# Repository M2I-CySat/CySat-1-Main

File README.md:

# CySat 1 - Make to Innovate at Iowa State University

**Onboard Computer (OBC) firmware, Satellite Systems, and Ground Station Software** - [CySat M2I](https://m2i.aere.iastate.edu/cysat/)

## Instructions
1. Navigate to the CySat-1 CyBox folder and read the documents under `/About CySat-1: README!` to gain a basic understanding of the CySat-1 mission, objectives, and project structure 
2. Continue reading this README to know basic files, instructions, and applications for each subsystem
3. Reference subsystem-specific setup instructions, guides, and data sheets to gain an understanding of your specific tasks found in the [CySat 1 box folder](https://iastate.app.box.com/folder/174137892065) under Subsystems -> [Subsystem]

## ADCS - Attitude Determination and Control System

**ADCS Testing Spreadsheets now in Box: Subsystems/ADCS/Tests**

- `CubeADCS - Commissioning Manual [V3.06]` - This document describes the activities related to the commissioning of a CubeSpace ADCS module in flight.
- `CubeADCS - Health Check [V3.15]` - This document will provide the instructions and results of the health check of the CubeADCS unit. The instructions provided must be followed exactly and the observed results must be indicated as is.
- `CubeADCS - ICD [V3.08]` - This document describes the characteristics of the CubeADCS unit as well as the mechanical and electrical interfaces to the bundle. CubeADCS units can be configured with different sensor and actuators for different mission requirements. This document covers all ADCS configurations and readers are to use their discretion in determining which parts are relevant to their various bundle configurations.
- `CubeADCS - Option Sheet (Y-Momentum) [V3.02]\_TGT` - This document include the complete ADCS solution for Y-momentum control. A momentum wheel (in various sizes) is included in the solution and can be mounted either on the bundle or separately from the bundle, depending on the size of the wheel. CubeSpace’s fine sun and nadir sensor module, CubeSense, can also be added to the solution if more accurate attitude control is required.
- `CubeADCS - Reference Manual [V3.10]` - This document serves as source of information to refer to when using the User Manual, Commissioning Manual, and other CubeADCS documentation. The document contains complete listings of TCs and TLMs, communications examples, and other reference examples to assist in designing a system which will interface with the ADCS.
- `CubeADCS - User Manual [V3.07]` - This document provide the user with instructions of completing the initial setup of the CubeADCS unit for the health check, instructions for connecting the unit to an OBC, a guide to mounting sensors inside a satellite and calculating mounting transforms, a functional description of the control modes that the CubeADCS unit is capable of executing, general usage instructions for all major functionality, and an overview of the hardware included in this bundle and their performance.

## CloneComm Ground Station

- See here: https://github.com/M2I-CySat/CloneComm/

### Command Manifest

See the full list of commands in CyBox

- Place commands under their respective type
- "#" marks the beginning of a subtype
- cmd_id:com_desc:data_payload(1=True,0=False):gs_sendable(1=True,0=False)

#### 10:OBC

0:Ping Response:1:0
1:Ping Request:0:1
2:Disable Beacon Response:1:0
3:Disable Beacon Request:0:1
4:Basic Health Check Response:1:0
5:Basic Health Check Request:0:1
6:Main Operating Response:0:0
7:Main Operating Request:0:1

#### 30:EPS

0:Voltage Response:1:0
1:Voltage Request:0:1

#### 40:SDR

0:Power Status Response:0:0
1:Power Status Request:0:1
2:Time Set Response:0:0
3:Time Set Request:1:1
4:Set RF Bandwidth Response:1:0
5:Set RF Bandwidth Request:1:1
6:Set Calibration 1 Response:0:0
7:Set Calibration 1 Request:1:1
8:Set Calibration 2 Response:0:0
9:Set Calibration 2 Request:1:1
10:Set DC Gain Response:0:0
11:Set DC Gain Request:1:1
12:Set fftsize Response:0:0
13:Set fftsize Request:1:1
14:Set Frequency Response:0:0
15:Set Frequency Request:1:1
16:Set Integral Response:0:0
17:Set Integral Request:1:1
18:Set Sample Rate Response:0:0
19:Set Sample Rate Request:1:1
20:Set spavg Response:0:0
21:Set spavg Request:1:1
22:Reset SDR to Default Values Response:1:0
23:Reset SDR to Default Values Request:0:1
24:SDR Values Response:1:0
25:SDR Values Request:0:1
26:Take Measurement Response:1:0
27:Take Measurement Request:1:1
28:Start Transfer Response:1:0
29:Start Transfer Request:1:1
30:File Finished Response:1:0

## EPS - Electrical Power System

- In this folder is all known versions of EnduroSat EPS documentation.
- Some of the documents contain inaccuracies: discrepancies in the diagrams and tables, but the ones at the root level are mostly correct
- The files in the Flash Drive folder are the ones that came directly from EnduroSat when the EPS was purchased, but there appear to be some inaccuracies here too, especially with the I2C manual
- The folder labelled inaccurate documents is kept for the sake of posterity

## OBC - Onboard Computer

The EnduroSat Onboard Computer Type II (Indicated as Type I on the OBC in the lab) includes the STM32F4x Microcontroller, various communication interfaces, peripheral I/O devices, a prototyping area, and a PC-104 stack connector. EnduroSat provides an Open Software SDK which is included in this repository in addition to the main CySat 1 mission program.

### Environment Setup

1. Dowloand [GitHub Desktop](https://desktop.github.com/) from the web and clone the CySat-1-Main repository within the app
2. Download and install STM32CubeIDE:

- Go to: [https://www.st.com/en/development-tools/stm32cubeide.html](https://www.st.com/en/development-tools/stm32cubeide.html)
- Select "Get Software" for the version that corresponds to your computer’s operating system
- Accept license agreement
- Enter first and last name, email, and check "I have read and understood the Sales Terms & Conditions, Terms of Use and Privacy Policy"
- Click "Download"
- Check email and click "Download now" on email, redirecting you to the website
- It might automatically start downloading. If it doesn’t, select "Get Software" again and it should start downloading

3. Open the installer and follow the installation steps
4. Launch STM32Cube and select a workspace folder that is NOT your GitHub repo location (the default location should be sufficient)
5. Open the cloned repo: `File > Open Project from File System > Directory > *navigate to repo location* > Make sure all folders are selected > Finish`
6. Update Software by going to `Help > Check for Updates`
7. Build the project by clicking the "Hammer" icon on the toolbar at the top
8. Happy Programming!

### Debug/Run Code on the OBC

#### The following items are required to debug, run, and deploy a program on the OBC (see CySat inventory)

1. Use the following:

- Pumpkin Board (or equivalent test bed equipped with a PC-104 stack connector + interface)
- Power Supply + barrell power cable for PSU (the OBC does NOT recieve power via its onboard USB interface, this is used for other purposes)
- ST-LINK v2 In-circuit Debugger + SWD cable (OBC <-> ST-LINK) + Mini-USB cable (ST-LINK <-> Dev computer)

2. Ensure the power supply is set to **7.8 V** and connected as shown in the image. Simply launch STM32Cube and debug away!

#### Then, in the STM IDE

3. Ensure you have the OBC_SDK project selected and click the "Run" (play) button, that's it!
4. For troubleshooting purposes, in debug/run configurations -> Debugger tab, make sure the ST-LINK S/N is filled in, the interface is set to SWD, and the reset behavior type is "Connect under reset"

#### Use PuTTY to debug OBC

The UART module on the OBC allows debug messages to be received using Serial protocol from a PuTTY terminal via use of the following function

```C
debug_printf("Your message goes here", [variables]); // This function can be used exactly like printf(); from the C <stdio> library
```

Then, to receive messages, perform the following:

1. Open and install [PuTTY](https://www.chiark.greenend.org.uk/~sgtatham/putty/latest.html)
2. Configure settings under `Session` according to the below image. _IMPORTANT_: Look in device manager to determine which COM port is in use by the OBC

3. Configure settings under `Terminal` according to the below image:

4. Configure settings under `Serial` according to the below image:

5. Save and load a custom CySat configuration for later use and click `Open`
6. Start the program and observe debug messages!

#### Use Onboard LEDs to debug OBC

Set the green and amber LEDs to different states depending on the state of the program

```C
debug_led_green(count, period); // Green light: Set the number of times the LED should flash (count)
                                // and the speed of the flash (period)
```

```C
debug_led_amber(count, period); // Amber light
```

## Payload SDR - Scientific Instrument + Radiometer Communication Device

- See here: https://github.com/M2I-CySat/CySat-1-Payload

## UHF/Antenna

- `Antenna deployment tester Rev 1.2pdf` - User manual designed to detail the antenna deployment tester. Can be useful for developing and testing I2C communications for the UHF antenna.
- `ES_UHF_Module_TestReport_0318TU211104.docx` - Shows the tested values at certain temperature, humidity and power supply voltage.
- `UHF type_II_ESTTC_Protocol_Rev_4.pdf` - This lists the commands we can supply to the uhf to receive the wanted values. Critical importance as they will be used for sending information out the antenna.
- `UHF_Antenna_II_User_Manual_data_interface_Rev_2.3.pdf` - User manual for the antenna specifically I2C communications
- `UHF_Antenna_II_User_Manual_Rev1.4_23112018.pdf` - General overview of the antenna. This lists its features and hardware layout in clear precise ways. (UHF band for communications is 435-438 MHz)
- `UHF_Antenna_III_Datasheet_Rev1.pdf` - Very similar to the user manual listed above. however this is for the Antenna III instead of Antenna II.
- `UHF_type_II_Datasheet_Rev_1.6.pdf` - Lists the features, Morse code is among them, as well as how to test this component on the earth and how it connects to the OBC and antenna.
- `UHF_type_II_UserManual_Rev_1.5_21112018.pdf` - Explains the connections and the features exactly like the previous document. This may just be an older copy of the datasheet above.
- `PuttyLogs` - This is the folder I have listed tests for. Working commands displayed in log files.

## Documentation Discrepancies

- In the EPS Datasheet, there are some extra pins such as the V_RTC and EPS_Reset which we do not believe we have for our hardware
- In the Manual version 1.1, the LUP 5v says it is on pin H1-48, but we have measured it as swapped with LUP 3.3v. To clarify, LUP 5v is on pin H1-51 and LUP 3.3v is on H1-48
- In the I2C manual version 2, there are diagrams showing hardware we do not have on our device.

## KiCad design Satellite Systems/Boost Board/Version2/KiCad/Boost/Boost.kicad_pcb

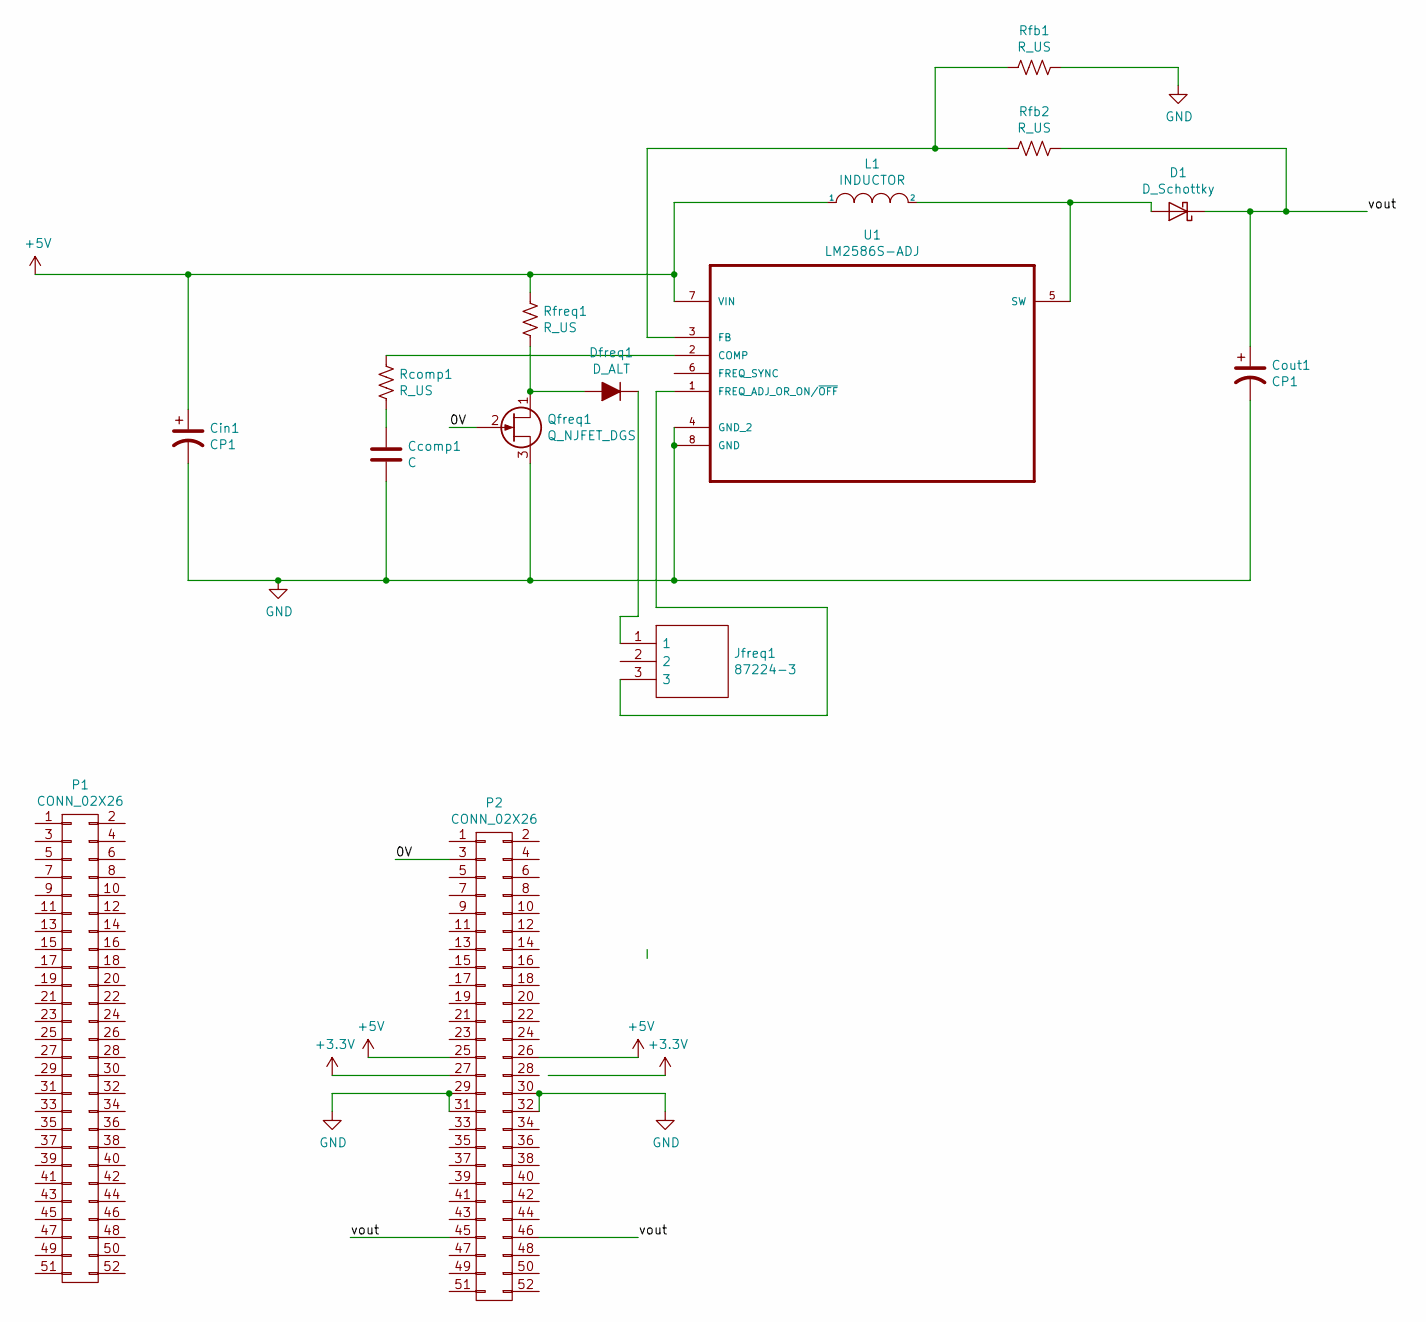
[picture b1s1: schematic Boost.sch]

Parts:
Ccomp1: C; C_1206_3216Metric
Cin1: CP1; C_1206_3216Metric
Cout1: CP1; C_1206_3216Metric
D1: D_Schottky; SODFL3617X108N
Dfreq1: D_ALT; D_1206_3216Metric
Jfreq1: 87224-3; 872243; Manufacturer_Part_Number 87224-3; Mouser Part Number 571-872243
L1: INDUCTOR; SDR0403
P1, P2: CONN_02X26; CSK_Header
Qfreq1: Q_NJFET_DGS; SOT95P237X111-3N
Rcomp1: R_US; R_0603_1608Metric
Rfb1, Rfb2: R_US; R_0603_1608Metric
Rfreq1: R_US; R_0603_1608Metric
U1: LM2586S-ADJ

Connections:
+3V3: P2.27
+5V: Cin1.1, L1.1, P2.25, P2.26, Rfreq1.1, U1.7 (VIN)
/0V: P2.3, Qfreq1.2 (G)
/vout: Cout1.1, D1.1 (K), P2.45, P2.46, Rfb2.1
GND: Ccomp1.2, Cin1.2, Cout1.2, P2.29, P2.30, P2.31, P2.32, Qfreq1.3 (S), Rfb1.1, U1.4 (GND_2), U1.8 (GND)
unnamed: Ccomp1.1, Rcomp1.2
unnamed: D1.2 (A), L1.2, U1.5 (SW)
unnamed: Dfreq1.1 (K), Jfreq1.1
unnamed: Dfreq1.2 (A), Qfreq1.1 (D), Rfreq1.2
unnamed: Jfreq1.3, U1.1 (FREQ_ADJ_OR_ON/~OFF)
unnamed: Rcomp1.1, U1.2 (COMP)
unnamed: Rfb1.2, Rfb2.2, U1.3 (FB)

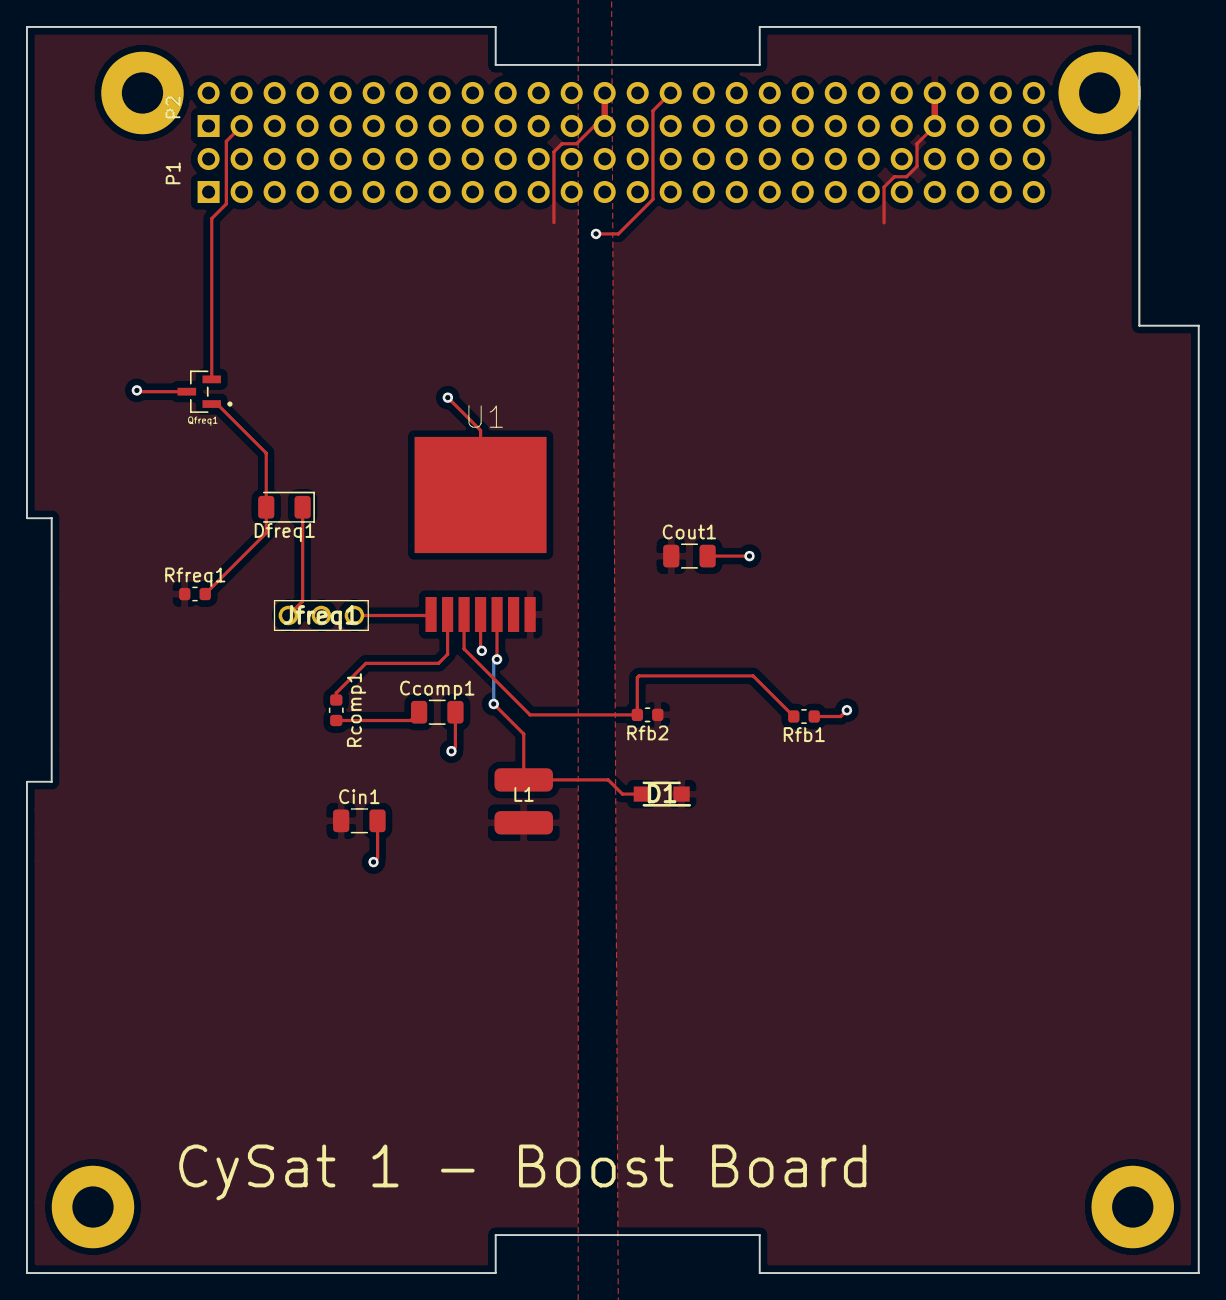
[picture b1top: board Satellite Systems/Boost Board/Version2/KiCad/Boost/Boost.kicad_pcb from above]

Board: 2 copper layers, 90.2 x 95.9 mm, 15 parts (0 on the bottom side), 11 nets.

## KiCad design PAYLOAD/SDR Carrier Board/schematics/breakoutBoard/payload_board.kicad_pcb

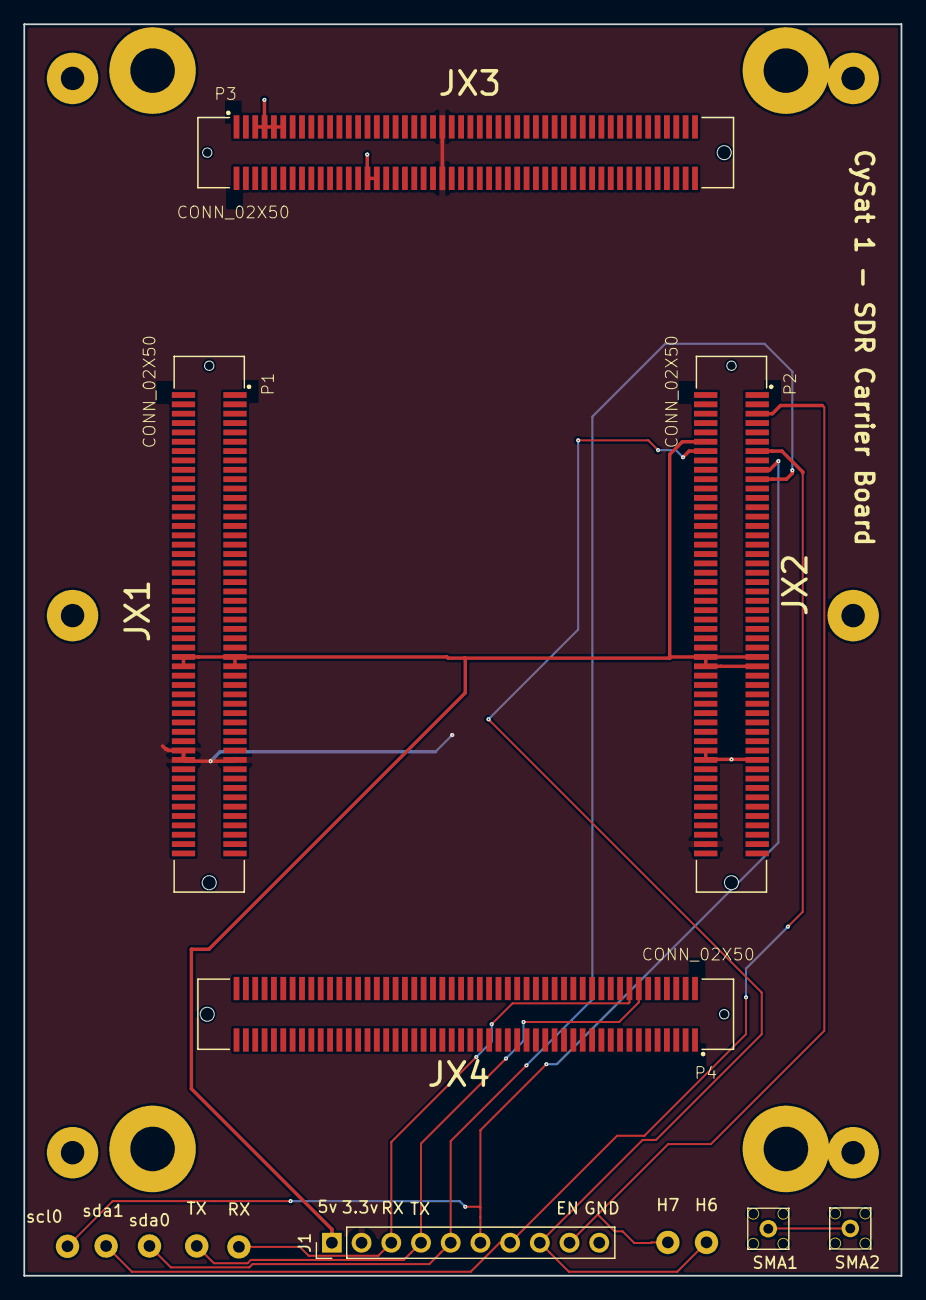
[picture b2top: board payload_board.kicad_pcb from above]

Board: 2 copper layers, 75.0 x 107.0 mm, 14 parts (0 on the bottom side), 11 nets.

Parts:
H6, H7: MountingHole_Pad; MountingHole_2.2mm_M2_Pad
J1: Conn_01x10; PinHeader_1x10_P2.54mm_Vertical
P1, P2, P3, P4: CONN_02X50; FCI_61083-101400LF
RX: MountingHole_Pad; MountingHole_2.2mm_M2_Pad
SMA1, SMA2: Molex-MMCX-SMD; Molex MMCX SMD 50Ohm
TX: MountingHole_Pad; MountingHole_2.2mm_M2_Pad
scl0: MountingHole_Pad; MountingHole_2.2mm_M2_Pad
sda0, sda1: MountingHole_Pad; MountingHole_2.2mm_M2_Pad

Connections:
/3.3v: J1.2, P1.78, P1.79, P1.80, P2.98, P3.45, P3.46
/5v: J1.1, P1.57, P1.58, P1.59, P1.60, P2.12, P2.57, P2.58, P2.59, P2.60
/ENABLE: H7.1, J1.9, P2.5
/GND: J1.10, P2.78, P2.79, P2.80, P3.5, P3.7, P3.9, P3.11, P3.30, P3.32
/SCL0: J1.6, P2.17, scl0.1
/SCL1: H6.1, J1.8, P2.14
/SDA0: J1.5, P2.19, sda0.1
/SDA1: J1.7, P2.13, sda1.1
/UART_RX: J1.3, P4.16, RX.1
/UART_TX: J1.4, P4.14, TX.1
unnamed: SMA1.1, SMA2.1

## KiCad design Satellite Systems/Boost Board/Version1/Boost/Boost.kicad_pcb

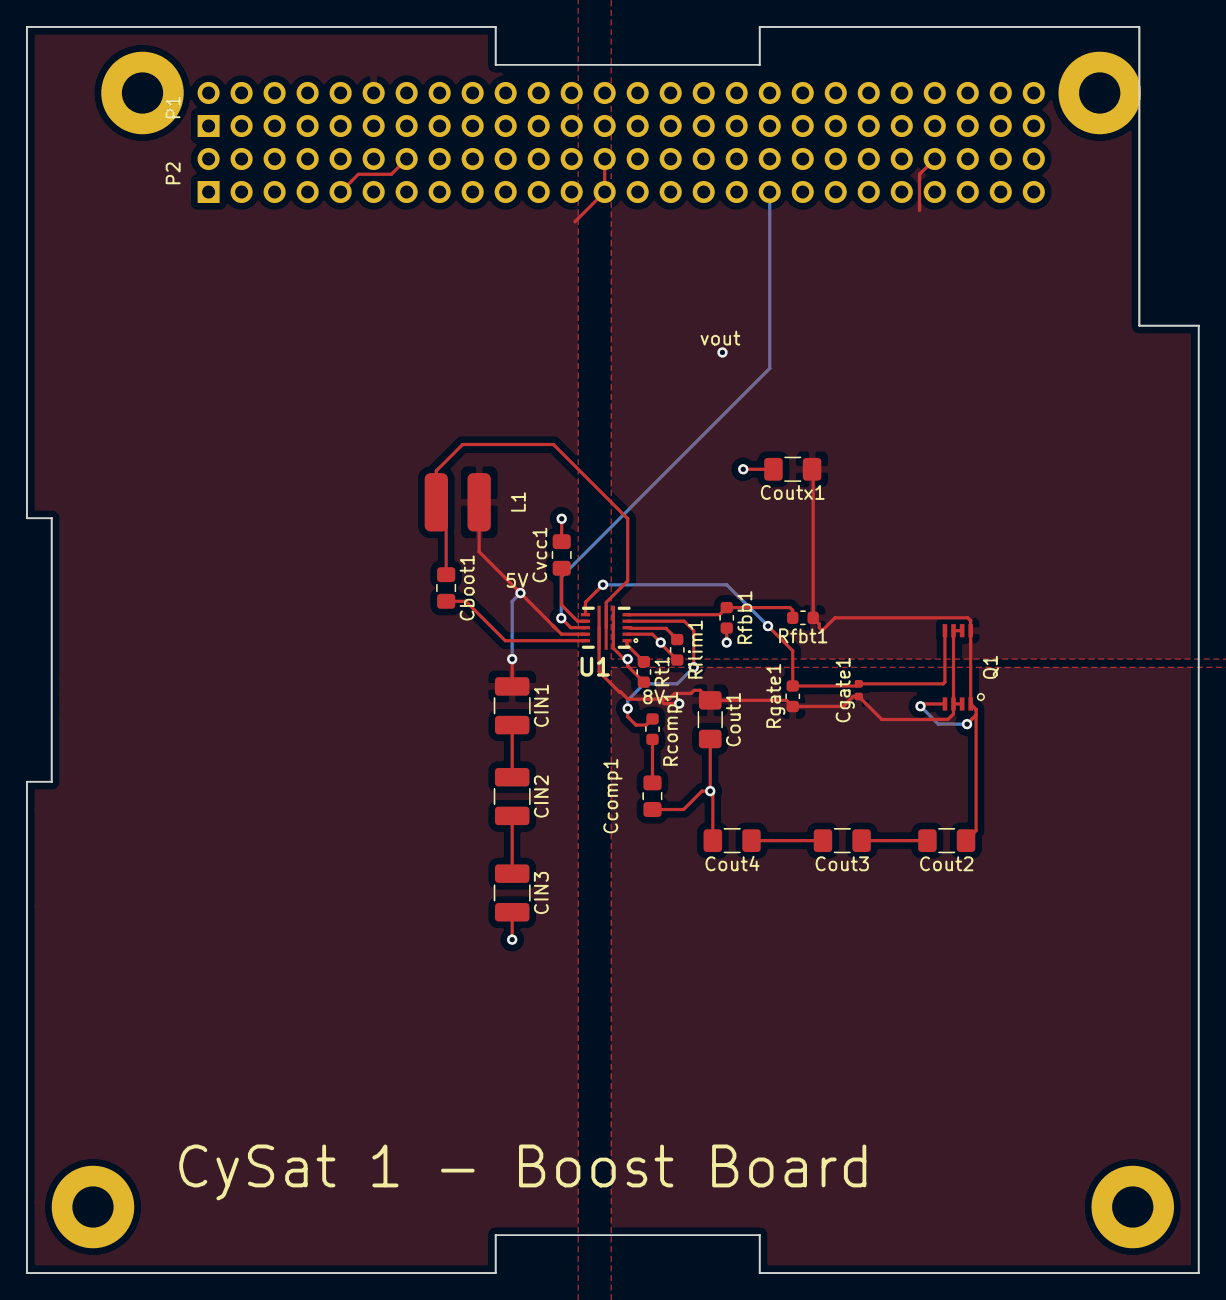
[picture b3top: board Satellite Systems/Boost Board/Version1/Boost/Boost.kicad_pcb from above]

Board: 2 copper layers, 90.2 x 95.9 mm, 23 parts (0 on the bottom side), 19 nets.

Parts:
CIN1, CIN2, CIN3: 10uF; C_1210_3225Metric_Pad1.42x2.65mm_HandSolder
Cboot1: 100nF; C_0805_2012Metric_Pad1.15x1.40mm_HandSolder
Ccomp1: 3.3nf; C_0805_2012Metric_Pad1.15x1.40mm_HandSolder
Cgate1: 22n; C_0402_1005Metric
Cout1, Cout2, Cout3, Cout4: 10u; C_1206_3216Metric_Pad1.42x1.75mm_HandSolder
Coutx1: 10u; C_1206_3216Metric_Pad1.42x1.75mm_HandSolder
Cvcc1: 4.7uf; C_0805_2012Metric_Pad1.15x1.40mm_HandSolder
L1: 2.7uH; SDR0403
P1, P2: CONN_02X26; CSK_Header
Q1: Q_PMOS_DGS; Si6423DQ
Rcomp1: 12.1k; R_0603_1608Metric
Rfbb1: 86.6k; R_0603_1608Metric
Rfbt1: 453k; R_0603_1608Metric
Rgate1: 162k; R_0603_1608Metric
Rilim1: 86.6k; R_0603_1608Metric
Rt1: 140k; R_0603_1608Metric
U1: TPS611781RNWR; RNW0013A

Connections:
+3V3: P2.27, P2.28
+5V: CIN1.1, L1.1, P1.12, P2.25, P2.26, U1.12
/+8V: Cgate1.1, Cout1.1, Q1.3, Rgate1.1, U1.8
/Boost_EN: P2.35, U1.11
/vout: Cout2.1, Coutx1.1, P2.46, Q1.1, Rfbt1.1
GND: CIN3.2, Ccomp1.2, Cout1.2, Cout4.2, Coutx1.2, Cvcc1.2, P2.9, P2.14, P2.17, P2.21, P2.22, P2.29, P2.30, P2.32, P2.47, P2.48, Rfbb1.2, Rilim1.2, Rt1.2, U1.2, U1.6
unnamed: CIN1.2, CIN2.1
unnamed: CIN2.2, CIN3.1
unnamed: Cboot1.1, L1.2, U1.7
unnamed: Cboot1.2, U1.13
unnamed: Ccomp1.1, Rcomp1.2
unnamed: Cgate1.2, Q1.2, Rgate1.2, U1.9
unnamed: Cout2.2, Cout3.1
unnamed: Cout3.2, Cout4.1
unnamed: Cvcc1.1, U1.10
unnamed: Rcomp1.1, U1.4
unnamed: Rfbb1.1, Rfbt1.2, U1.5
unnamed: Rilim1.1, U1.3
unnamed: Rt1.1, U1.1

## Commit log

2022-03-23 Initial dump from ECpE Senior Design
    Initial dump from ECpE senior design files. This is moving files from ECpE's GitLab server to a more public GitHub server.
2022-09-20 Adding documentation
2022-09-20 update to gitignore
2022-09-21 fixed - OBC compilation error
2022-09-22 r2u2 Compiles now
    Added FFTW3 lib
2022-09-30 Remove old SDK projects (archived in branch)
    Remove old SDK projects (archived in branch)
2022-09-30 Settings environment changes
    Settings environment changes
2022-09-30 OBC SDK error fix
    OBC SDK error fix: function missing arguments
2022-10-03 Moved docs to CyBox
    Moved all documentation to CyBox for consistency
2022-10-05 Remove discoboard and R2U2misc
    Remove discoboard and R2U2misc
2022-10-05 Update ADCSFunctions.c
    Added alpha, beta, and gamma angles for magnetometer deployment and inserted the angles into TC_33
2022-10-05 Remove OBC README
2022-10-13 Some of the work for the EPS Battery Capacity Functions.
    Added more values to the battery measurement struct and added the first half of the addNewBatteryMeasurement funciton.
2022-10-16 Updated Python Pillow dependency and added todo for communications
2022-10-16 Did some transmission and reception stuff that may not be needed, and worked on the startup sequence.
2022-10-16 Project restructuring (for OBC test)
2022-10-16 OBC file fix
2022-10-18 Document instructions to debug/run/deploy on OBC
2022-10-20 Added functions to flash lights for debugging purposes.
2022-10-20 Added todos for beacon, detumbling, health checks
    Added todos, changed printf statements to debug_printf so status messages can be displayed while debugging
2022-10-21 Use default DEBUG_ENABLE program for light blinking test
2022-10-22 Test LED debugging program works properly with task threading
2022-10-22 Cleaned up the code and adjusted LED flashing
2022-11-09 Tweaked some startup stuff and began implementing communications
2022-11-10 Did comms tests, didn't work
2022-11-13 Added GUI buttons for SDR, UHF functions (Python)
2022-11-13 Minor debug changes, UHF still doesn't work
2022-11-15 More mostly meaningless debug changes, commented some stuff out
2022-11-16 More debug changes mostly to set_beacon_text()
2022-11-16 Clean up SET_BEACON_TEXT() to better debug 11/16
2022-11-16 Debugging UHF commands
2022-11-17 Added 30 minute mission delay
2022-12-03 I don't know what I did but the UHF commands are working now
    UHF beacon commands (start, end, set period, set text) are working despite not showing up properly in Putty. The satellite may need to be restarted a few times for it to work properly. The get UHF te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
2023-02-04 Rewrote some debug statements
2023-02-04 Additional stuff 2
2023-02-10 Better debug prints
2023-02-11 Fix language for debugging OBC on pumpkin board
2023-02-11 Directory fix
2023-02-12 Formatting
2023-02-12 Add debug info to README
2023-02-16 Added more SDR commands to command manifest
2023-02-16 More debug printf stuff
2023-02-16 Added failure point marker for ADCS Loop
2023-02-16 Onboarding things
2023-02-18 Debugging tasks
2023-02-18 Update .gitignore (untrack IDE files)
2023-02-18 Drivers
2023-02-21 Improved debug messages in AppTasks for better testing and modified UART callback
2023-02-23 Hopefully added error handling to the ADCS while loop
2023-02-23 Additional ADCS error handling, now exits function and gives error message
2023-02-23 Move old ground station to archive repo
2023-02-23 Directory change
2023-02-23 File structure re-organization
2023-02-25 UHF Verification and attempting to get the ADCS to do something
2023-02-25 Tried %x for ADCS, gives data but nonsencical data
2023-02-26 Move COMMS docs from repo into COMMS box folder
2023-03-02 Did some debugging stuff
2023-03-09 9600 Baud on UHF
2023-03-09 Debugging UHF pipe transmit and recieve on UART
2023-03-09 Comms Stuff
2023-03-09 Did more comms stuff
2023-03-23 Fixed ADCS_TELECOMMAND
2023-03-24 Comms testing
2023-03-24 Changed back to packet transmission
2023-03-25 CySat Packet testing for UHF transparent mode
2023-03-30 ADCS testing 3/29
    too many bugs
2023-04-06 Added debugging stuff to telemetry
2023-04-06 Fixed debug for ADCS_Telemetry
2023-04-07 Some additional testing code
2023-04-13 just tested tlm
2023-04-14 Code_Seperator
    Added code for the code seperator
2023-04-14 Update Payload.c
    Added a helper method to figure out the size of the file
2023-04-14 Data file number assignment
    Added code (currently untested) to create a new file each time a set of data is produced; the files will be produced in number order
2023-04-16 Updated code_seperator
2023-04-16 Testing code_seperator
2023-04-16 Fixed FILE_TRANSFER errors
    Fixed fatal errors in file transfer code and added it to AppTasks.c for future testing and development
2023-04-20 Comms testing and ADCS counter emergency loop escape
2023-04-21 Continued work on file handling code
    Edited the code for writing to the SD card (currently untested, but has no errors) and removed some unused files from the repository
2023-04-22 Ignore release/
2023-04-22 Implement UHF Tx/Rx task to receive commands and reply with a response (needs testing)
2023-04-22 Move Payload and Boost Board to seperate repos
2023-04-22 Move UHF firmware to CyBox
2023-04-22 Add submodules for payload and ground station
2023-04-23 CODE_SEPERATOR
2023-04-23 Added basic testing for Code_Seperator
2023-04-23 removed packet_size()
    Contains the use of file_size which doesn't exist, function overall isn't used.
2023-04-24 Test interrupt-based UART communication
    Setup receive callback with driver
2023-04-27 Code now writes numbers to a file
    The code is now able to write to a file on the SD card; however, it cannot yet read any number stored there
2023-04-27 Continuing work on reading from file
2023-04-28 SD card read write works.
2023-04-28 Minor fix
2023-04-29 Started work on function to delete file
    Added a function to delete a specified (given by data entry number) data or Kelvin file from the SD card. Currently needs testing
2023-05-05 Payload code separator doesn't work
2023-05-05 Not working but closer to working
2023-05-05 Also doesn't work lol
2023-05-05 aaaaa
2023-06-01 Made stuff neater and fixed a few payload errors.
2023-06-01 Update Payload.c
    add author
2023-06-01 Update Payload.c
    Create method for deleting files
2023-06-01 Update Payload.c
    accidentally forgot the parentheses
2023-06-01 Minor changes cleaning up the transmission function
2023-06-06 Please work
2023-06-06 Added requirements to middleman instead of non functional venv
2023-06-06 Added basic delays and such
2023-06-06 Added test dat and kelvin files
2023-06-06 Update middleman.py
    commenting
2023-06-06 Maybe fixed serial stuff?
2023-06-09 Some packet_separator fixes and minor delete and ADCS testing
2023-06-15 Rewrote the file delete functions using FATFS functions and added some more descriptive error checks
    Hope to test it Friday
2023-06-15 Extra thing that didn't make it in
2023-06-15 update stuff temp
2023-07-05 Not sure what I did this was days ago
2023-07-06 Update BatteryCapacity.c
    Battery Capacity Recharge
2023-07-06 Fixed some transmission stuff, its weird
2023-07-11 Minor bugfixes
2023-07-11 Take twelve of just adding 2 files
    Wrong spot but the other spots won't work
2023-07-11 Beginning of ax.25gen
2023-07-11 Started to add the contents of the AX.25 contents
2023-07-13 fixing battery recharge
2023-07-13 Hopefully fixed some transmission logic
2023-07-18 forgot to push oops
2023-07-19 Composer
    Composer: Sort each of the data types by if they're satellite data or packet data. Convert portions of it from hex to decimal to Sort by Packet ID and Measurement ID. Compile Packet data in a string 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
2023-07-20 Creating files for different measurements
2023-07-20 fixing recharge funciton
2023-07-21 Composer debugging
    Fixed Composer
2023-07-22 Update composer.py
    debugging
2023-07-25 Packet separator testing(I broke it) and ax.25 creation
2023-07-26 Hopefully functional ax.25 generator
2023-07-26 Update composer.py
    Organization of composer messages
2023-07-28 updating composer
2023-07-30 ADCS tests and OBC Interrupt tests
2023-08-01 Ground Station Commands
    Got rid of beacon commands that shouldn't be there.
    Added comments and cases for all of the UHF commands
2023-08-03 Fixed a bug in groundstation.c
2023-08-03 composer
2023-08-03 Didn't aaaahhh
2023-08-03 todo statements
2023-08-03 Fix ping response
2023-08-03 Ground Station commands
2023-08-05 Fixed parseCySatPacket to deal with ax.25 content instead of plaintext
2023-08-07 Delete file taking up lots of space
    Not sure why 100kb of stuff is causing us to go over our data caps by 250% but ok
2023-08-07 Ground Station UPS responses
    Doing my best. There may be an issue regarding pointers.
2023-08-07 Ground Station fixing
    edited comments, removed duplicates
2023-08-08 More packet generators and attempting full circuit comms
2023-08-18 A lot of stuff
    I wrote this a week ago and forgot to commit
2023-08-19 Communications works now. ADCS testing too;
2023-08-21 Clean up
2023-08-21 Added empty packet checker, and cleaned up a lot of debug printf
2023-08-21 Minor fixes
2023-08-22 Move middleman to CloneComm
2023-08-22 Removed GNU submodule (moved to CloneComm)
2023-08-22 New submodule organization
2023-08-22 Updates to comms
2023-08-26 Moved cysat packet to CloneComm
2023-08-26 New Payload commits
2023-08-26 Update README.md
    Cleaned up where to find things
2023-08-29 3/4 of major communications issues fixed
2023-09-03 File lister
2023-09-05 Fixed packet separator crashing satellite
    Both comms systems work again
2023-09-11 File Lister and RAM fix
2023-09-17 Comms upgrades
2023-09-17 Comms Fixes
2023-09-19 ADCS Debug code and start of packet separator rework
2023-09-19 Anotehr adcs sthing
2023-09-19 updated adcs code
2023-09-19 updated tc_44 based on ADCS user manual
2023-09-26 Added scrambling to packet_separator
2023-09-28 Working scrambler
2023-10-03 Some take image functions
2023-10-09 implemented ADCS telecommands
2023-10-09 Health checks and auto restart
2023-10-09 Some ADCS case switch fixes and additions and changes
2023-10-16 I don't remember
2023-10-17 Fixed some startup things
2023-10-17 formatted UHF print statements
2023-10-17 Fix EPS Health Check
2023-10-17 Attempted to fix UHF health checks
2023-10-19 Antenna status debugging
2023-10-21 ADCS Health Check
2023-10-21 UHF Health Checks
2023-10-21 small tweaks
2023-10-21 fixed typos
2023-10-21 Minor changes
2023-10-29 set restart to every 2 minutes
2023-10-29 ADCS debug code
2023-11-06 Minor changes and save unix time
2023-11-06 Updated some command values
2023-11-06 Updated return packet values
2023-11-07 Changed some signs for python compatibility and fixed not seeking packet_separator
2023-11-11 Fixes to ADCS Telecommand and increment
2023-11-12 Minor ADCS Tests
2023-12-05 New way of doing measurements
2024-03-22 Payload comms support and testing
2024-03-24 Test
2024-04-01 Payload tests and debugging
2024-04-03 Payload almost works but then I fried the OBC
2024-04-03 Rewrote the entire satellite to use RAM instead of SD Card
2024-04-03 Other two health checks support
2024-04-03 Health check relocation and TES file transfer system
2024-04-05 File transfer and ADCS mutex fixes
2024-04-09 Power checks, backup antenna deployment, an ADCS fix, and restart polling
2024-04-11 Power recovery fixes and some packet separator tests/debugging
2024-04-11 Trying to fix a github thing
2024-04-11 Update CloneComm
2024-05-05 FLIGHT CODE. All RBFs uncommented. Godspeed, CySat.
